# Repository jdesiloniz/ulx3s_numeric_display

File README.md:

# ulx3s_numeric_display

The goal of this project is to be able to use 4-digit 7-segment displays with the [ULX3S FPGA board](https://ulx3s.github.io/) as an easy and quick method of debugging/data display. OLED screens are really convenient but they require more complex logic and memory buffers to contain the graphical data, so I think having these displays as an alternative for simple debugging can help a lot for quick iteration and debugging.

## Design

In order to be able to interface one of these displays you need 12 pins, so the design uses two 74HC164N serial-to-parallel ICs to be able to interface all pins using just 4 data signals (+ VCC/GND). Segment data and digit data are generated at a pre-defined rate (by default in this design - 400Hz) and fed to these chips that rely them to the display. Only some transistors and resistors are required besides these connections to make it all work.

This design is meant to work with a common-anode display by default. Using common-cathode display is possible though, just changing the value of `COMMON_ANODE` to `1'b0` in the appropiate modules.

## Components

- `clk_divider`: configurable clock divider used to drive the 74HC164N (at 6MHz) and the refresh rate for the LED display.
- `shifter`: a shifter module that's able to perform multiple shift/rotation operations.
- `reset`: simple reset controller.
- `wb_hc164`: module that interfaces communication with **74HC164N** ICs using a simplified Wishbone bus.
- `led_display_controller`: module to drive the LED display through two 74HC164N. Users can place raw segment data for each one of the digits.
- `numeric_led_display_controller`: small wrapper on top of the previous module. Users just need to pass a 16 bit number and it'll be displayed in hexadecimal form by the LED display.
- `top`: an example of using these, displaying a second counter.

## Board

Warning: the PCB hasn't been tested yet, but the design has been found to work using a breadboard. I'll update this as soon as I get it built and running :). If in any case you want to play this, KiCAD design files are [available here](board).

The board is intended to be used with a common-anode display. Using a common-cathode display is possible but it'd require to change the layout of the transistors (to use NPN ones).

## Use

You're free to use any of these modules for your own projects, modify them or whatever. But it'd be nice if you at least drop a mention! Also, I can't guarantee that this won't break anything... it didn't in my case! :D

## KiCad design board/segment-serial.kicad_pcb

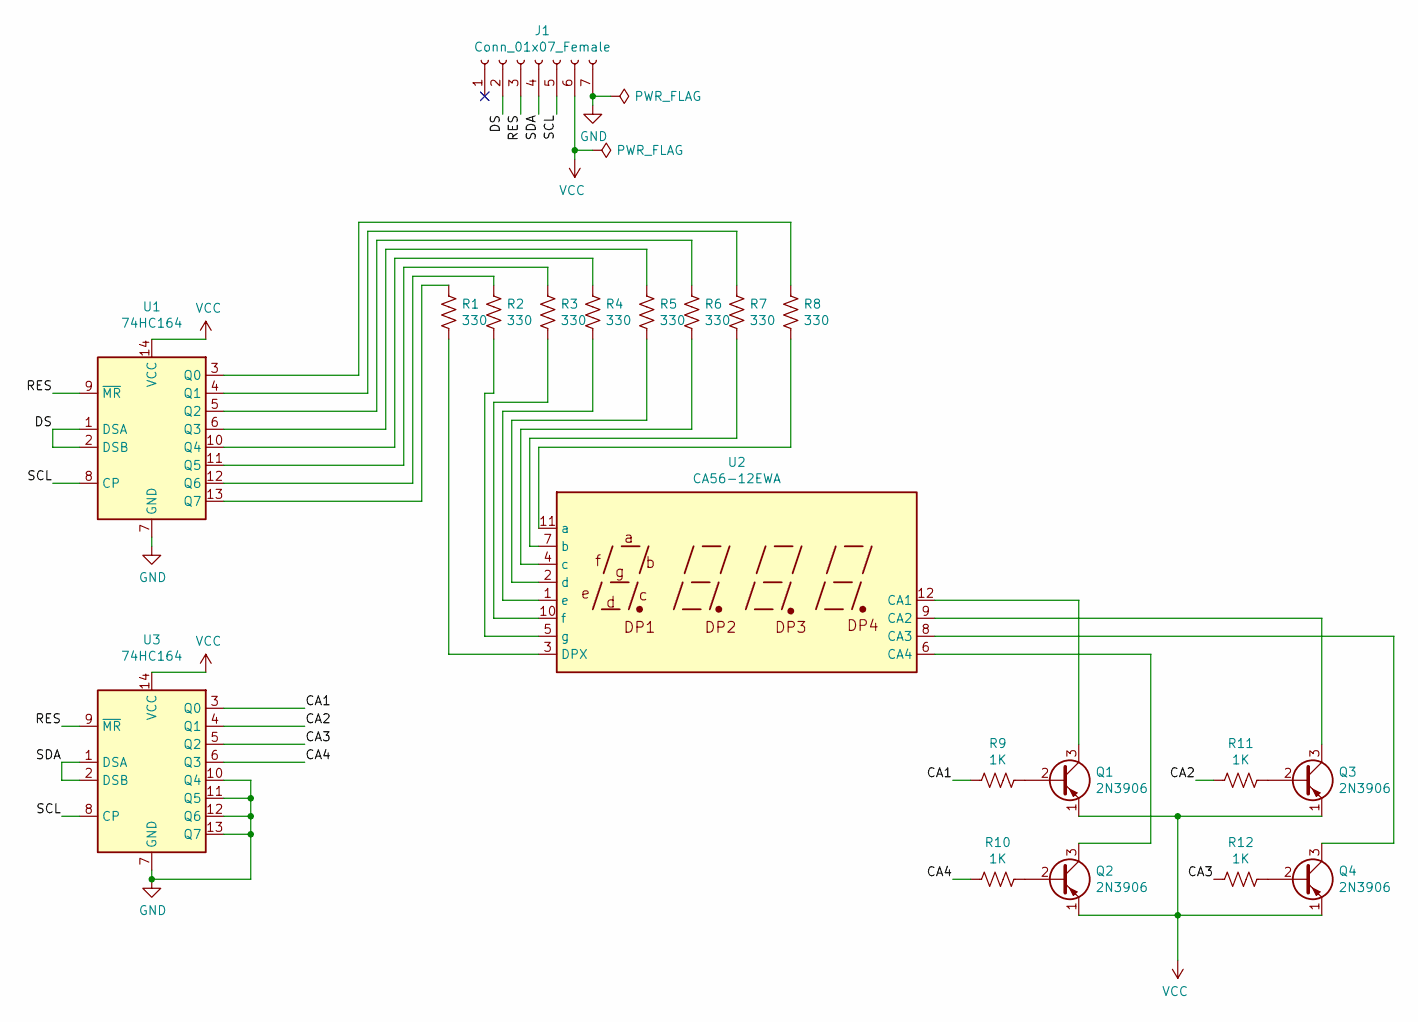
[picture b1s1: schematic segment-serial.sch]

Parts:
J1: Conn_01x07_Female; PinHeader_1x07_P2.54mm_Vertical
Q1, Q2, Q3, Q4: 2N3906; TO-92_Inline
R1, R2, R3, R4, R5, R6, R7, R8: 330; R_Axial_DIN0207_L6.3mm_D2.5mm_P7.62mm_Horizontal
R9, R10, R11, R12: 1K; R_Axial_DIN0207_L6.3mm_D2.5mm_P7.62mm_Horizontal
U1, U3: 74HC164; DIP-14_W7.62mm
U2: CA56-12EWA

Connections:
/CA1: R9.2, U3.3 (Q0)
/CA2: R11.2, U3.4 (Q1)
/CA3: R12.2, U3.5 (Q2)
/CA4: R10.2, U3.6 (Q3)
/DS: J1.2, U1.1 (DSA), U1.2 (DSB)
/RES: J1.3, U1.9 (~MR), U3.9 (~MR)
/SCL: J1.5, U1.8 (CP), U3.8 (CP)
/SDA: J1.4, U3.1 (DSA), U3.2 (DSB)
GND: J1.7, U1.7 (GND), U3.7 (GND), U3.10 (Q4), U3.11 (Q5), U3.12 (Q6), U3.13 (Q7)
unnamed: Q1.2 (B), R9.1
unnamed: Q1.3 (C), U2.12 (CA1)
unnamed: Q2.2 (B), R10.1
unnamed: Q2.3 (C), U2.6 (CA4)
unnamed: Q3.2 (B), R11.1
unnamed: Q3.3 (C), U2.9 (CA2)
unnamed: Q4.2 (B), R12.1
unnamed: Q4.3 (C), U2.8 (CA3)
unnamed: R1.1, U2.3 (DPX)
unnamed: R1.2, U1.13 (Q7)
unnamed: R2.1, U2.5 (g)
unnamed: R2.2, U1.12 (Q6)
unnamed: R3.1, U1.11 (Q5)
unnamed: R3.2, U2.10 (f)
unnamed: R4.1, U1.10 (Q4)
unnamed: R4.2, U2.1 (e)
unnamed: R5.1, U1.6 (Q3)
unnamed: R5.2, U2.2 (d)
unnamed: R6.1, U1.5 (Q2)
unnamed: R6.2, U2.4 (c)
unnamed: R7.1, U1.4 (Q1)
unnamed: R7.2, U2.7 (b)
unnamed: R8.1, U1.3 (Q0)
unnamed: R8.2, U2.11 (a)
VCC: J1.6, Q1.1 (E), Q2.1 (E), Q3.1 (E), Q4.1 (E), U1.14 (VCC), U3.14 (VCC)

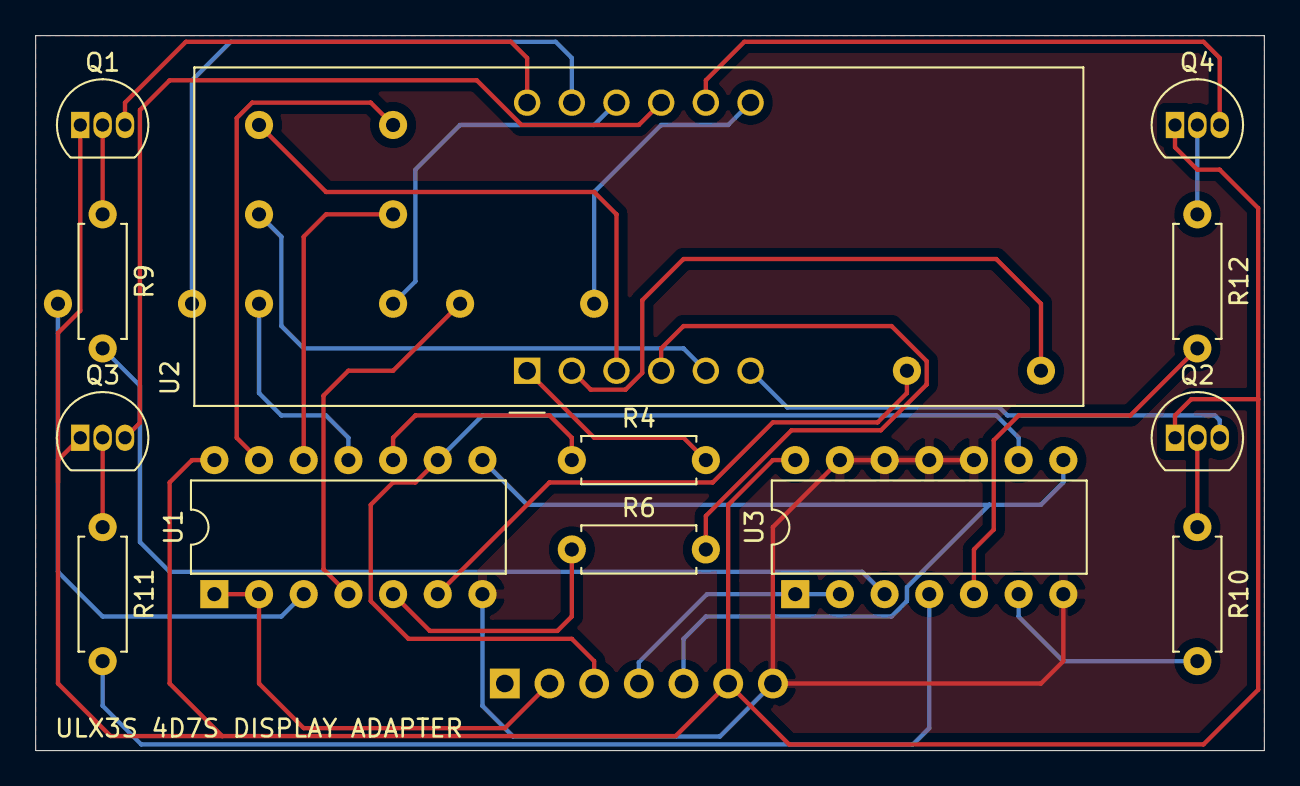
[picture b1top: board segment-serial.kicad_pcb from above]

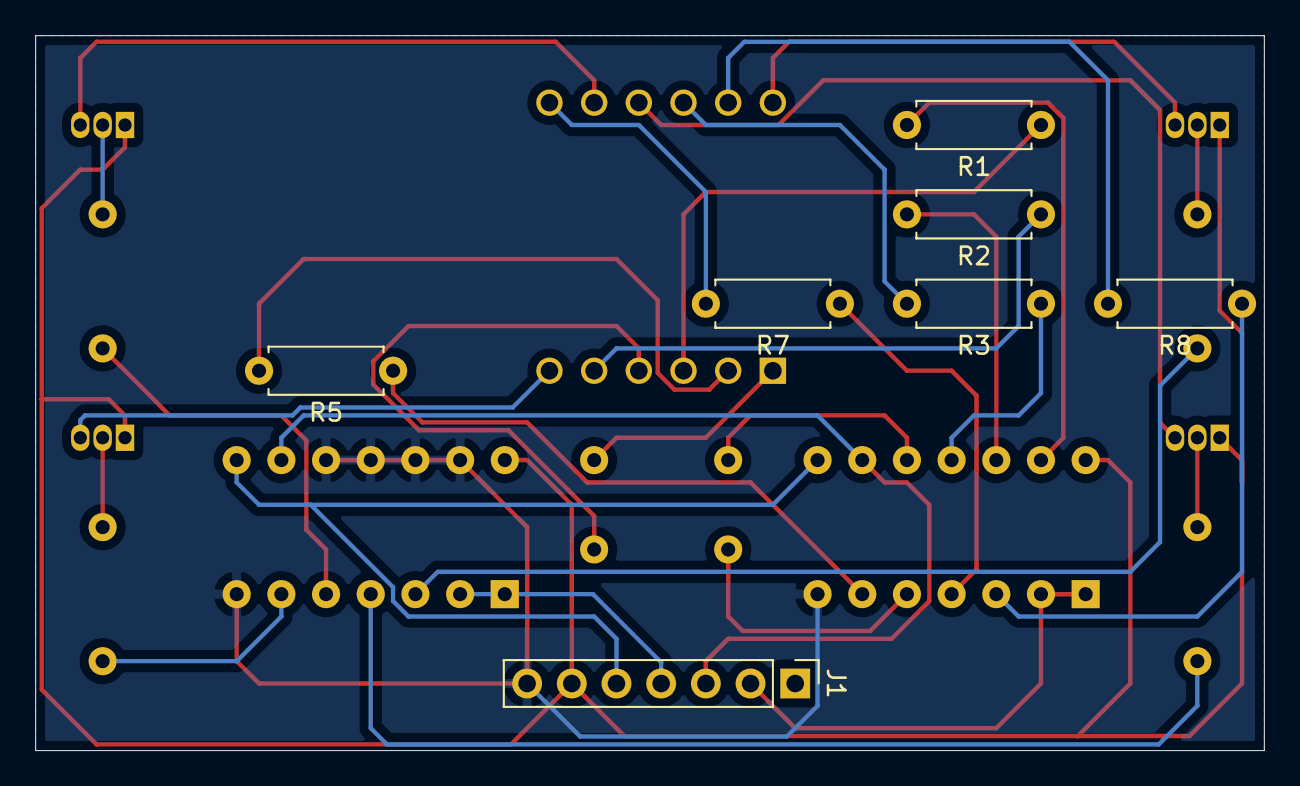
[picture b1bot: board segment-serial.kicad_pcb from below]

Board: 2 copper layers, 69.8 x 40.6 mm, 20 parts (7 on the bottom side), 34 nets.

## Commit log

2020-12-03 Add initial wait after resetting HC164 - at least 25ns required
2020-12-05 Fixed issues with LED display controller - added simulation code
2020-12-05 Adding support for common_anode/common_cathode displays
2020-12-05 Added led counter
2020-12-05 Adding top, failures in build process
2020-12-06 Fixed combinational loop issues with wb_hc164
2020-12-06 Fixed combinational loops
2020-12-07 Fixed issue with reset signal in led controller
2020-12-07 Fixing issue with unconnected pins in U3
2020-12-07 Added README.md
2020-12-07 Typo
2020-12-07 Clarifying supported kind of display
2020-12-07 More clarifying
2020-12-07 Fixing broken formal verification tests after changes to fix combinational loops
